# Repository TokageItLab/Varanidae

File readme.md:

# Varanidae

## Consepts / Ideology

This keyboard layout may look pretty Mad and Hacky at some parts, but there are proper reasons for each of them.

<details>
<summary>Simple implementation</summary>

We are not electronics professionals and do not like to implement complex PCBs. SMT may be efficient in using reflow, but it is hard for beginners, so we only use Through-hole components.

And to make implementation easier, we need to adopt Elite-C. However, Elite-C requires more space, so we solved this problem by overlapping it with other switches using a tall pin header.

In addition, to simplify the CNC manufacturing process, we had to design a case that could be machined with a 3-axis CNC. This makes it possible to output cases with some CNC services without complex communication with the manufacturers.

</details>

<details>
<summary>Compact layout for international</summary>

When we work, we place the pen tablet in front of the keyboard, thus making the desk smaller. So we needed to make the keyboard as compact as possible.

So we omitted some **outdated** keys (PauseBreak/ScrollLock/Insert/CapsLock) and adopted a 6U space bar. This allows us to provide almost a full keyboard (or more) functionality and place keys for language switching.

</details>

<details>
<summary>Left-side pad</summary>

We work with Blender and a pen tablet. Then, we hold the pen in our right hand, so we prefer to place the numpad (which has a lot of camera shortcuts assigned) in the left-side of the keyboard.

</details>

<details>
<summary>F13-F24 keys</summary>

We favor the F13-F24 keys for shortcuts. They avoid conflicts with the default shortcuts of any software and they are useful for resident application shortcuts.

I recommend to all keyboard manufacturers worldwide to implement F13-24 keys instead of having macro keys, or to allow F13-F24 keys to be assigned to the macro keys.

</details>

<details>
<summary>Backspace and Enter are the end of the right</summary>

We do not want to make more distance between the mouse, trackball, or trackpad and the keyboard. Also, since we use the Backspace and Enter keys so often, having them to the right of those keys can cause us to press other keys by accident.

Moreover, as an overlooked point, if the right-side of the Backspace and Enter keys are free, we can put our hand there to rest.

</details>

<details>
<summary>Lined up arrow keys</summary>

On common keyboard layout them in an inverted T-shape, but on some keyboards they are frequently in a single row to omit spaces.

However, in that case, the order is generally: "Left", "Down", "Up", "Right".

Perhaps this is because that, when you play games that use the arrow keys with the index finger in the Left and ring finger in the Right home position, the middle finger muscle tendon is pulled toward the ring finger.

But out of the game, this is unnatural considering the affordances. In the script editor, Up means "back a line", so we think it would be more natural to have it next to Left which means "back a character".

So this keyboard adopts the order: "Left", "Up", "Down", "Right" as default.

</details>

<details>
<summary>Compressed numpad</summary>

We should not need uselessly large + and Enter keys on numpad. More to the point, NumLock is not needed either. In that case, four basic math symbols can be placed vertically in one column.

Also, in fact, it is possible to place the Home/End/PgUp/PgDn keys symmetrically with those four keys, so we integrated them into one island.

This makes it possible to place keys for line transitions or Blender shortcuts without placing them to the right of Backspace and Enter.

</details>

<details>
<summary>R4 Tilda</summary>

The last mad point is that placing the Tilda at the end of R4. Because it is not used that often or the cases where it is used are quite special.

I believe that it is most reasonable to put Tilda at the end of R4. You may see a layout similar to this on some keyboards, such as Toshiba - Dynabook, but I don't understand why R4 Tilda is not more common.

I am saddened that there is no R4 Tilde in any GMK sets (and the same applies to the keys in the columns at both ends of compressed numpad).

</details>

Now, we finally got a keyboard that is very reasonable for us.

We hope that this layout will become more common and that the R4 Tilde will be included in some GMK set, so we are releasing it as an open source keyboard.

The license is all that is written in this repository, so this is no needed thing, but if you have any information about a derivative product of Varanidae or the R4 Tilde, we would be glad to hear about that.

Of course, simple feedbacks are also welcome.

## Supported layout

The rotary encoder is assigned to the middle click and vertical scrolling by default.

Varanidae supports [VIA](https://usevia.app/), so the key/encoder assignments can be changed.

---

**Note:** This keyboard is mainly designed for Japanese users, but uses the US layout. If you are using a JIS keyboard on the system, you will need to select the US keyboard layout (101/102 keys keyboard) in the "Language Settings".

**For example in Windows 10:**

「設定」→「時刻と言語」→「言語」→「優先する言語」→「日本語: オプション」→「ハードウェア キーボード レイアウト」→「レイアウトを変更する」→「英語キーボード (101/102 キー)」

---

## Description

This repository contains:

- case
  - ai
    - Vector file of the plates
    - **The plates are assumed to be 2mm thick, please note when ordering plates using this file**
  - f3d
    - Fusion 360 project file of the case
  - step
    - STEP files for CNC, output from Fusion 360 project
    - It may be necessary to refer to the Fusion 360 project to determine the exact hole type
    - **If you make the order with these files, pay attention to the type of threaded holes[^1]**
- img
  - Images for the readme
- pcb
  - kicad
    - KiCad project files of the PCB (include exported Gerber files)

Is ordering CNC expensive and complicated? [Varanidae Soul](https://github.com/TokageItLab/Varanidae_Soul) the simplified version of Varanidae only requires acrylic plates and screws. It is reasonable choice to try the Varanidae layout.

## Other required components

### For the PCB
- MX Keycap set x1 (**6u centerd space is required**)
- MX stabilizer set x1 (**6u wire is required, PCB mounted is required if you use hybrid layout**)
- MX stem switches x110
- Diodes 1N4148 x110
- Rotary encoder EC11 x1 (EC11N1525404 or EC11N1525402 is recommended)
- Knob x1 (**14mm diameter or less are strongly recommended since the case hole diameter is 15mm for the knob**)
- Elite-C x1
- Pin headers 5mm height x29 (For Elite-C, so **x11 + x11 + x7** or **x12 + x12 + x5** is reccomended)

---

**Note:** If you don't use the "spring" pin headers and need to solder the pin headers to the PCB, be careful about the working sequence. You must solder only the pin headers before mounting the switch, and the Elite-C must be soldered after the switch is mounted.

---

### For the case

#### To screw the case and the main plate
- M3 screws 15mm x20

#### To screw the bottom plate
- M3 screws 8mm x4
- M3 pipe spacers 4mm x4

#### To assemble the case legs with screws
- M5 full thread screws 34mm x2
- M5 pipe spacers 20mm x2
- M5 cap nuts 4mm depth x2

---

**Note:** The length of the case leg screw should be calculated based on the length of the leg and the depth of the cap nut you wish to use. For example, the screw and nut length are calculated as follows:

```
screw length (34mm) = spacer length (20mm) + cap nut depth (4mm) + depth of the case threaded hole which will be inserted the screw (10mm)
```

---

## Using libraries

- [kbd](https://github.com/foostan/kbd) - foostan (MIT license)
- [keebio-components](https://github.com/keebio/keebio-components) - Keebio (MIT license)
- [Keebio-Parts.pretty](https://github.com/keebio/Keebio-Parts.pretty) - Keebio (MIT license)
- [KiCad Footprint Libraries](https://gitlab.com/kicad/libraries/kicad-footprints/-/tree/master?ref_type=heads) - KiCad ([KiCad Libraries License](https://gitlab.com/kicad/libraries/kicad-footprints/-/blob/master/LICENSE.md))
- [MX_Alps_Hybrid](https://github.com/ai03-2725/MX_Alps_Hybrid/tree/master/Alps_Only.pretty) ([my fork](https://github.com/TokageItLab/MX_Alps_Hybrid/tree/Varanidae)) - ai03 (MIT license)

## Special thanks (Artisan keycaps for the thumbnail)

- Birb - [KEYMAKER](https://www.keymakerartisankeycaps.com/)
- Space 無 - [GEEKKEEY](https://www.instagram.com/geekkeey/)
- The 925 - [THOK](https://thok.design/)
- THINK - [BOXXX KEYCAP](https://boxxx.booth.pm/)

## License

MIT license except that the Tokage IT Lab.'s logo is CC BY-NC-ND 4.0. This means that if you want to manufacture and sell the derived PCBs, you can do so by removing the Tokage IT Lab.'s logo from them[^2].

Also, if you redistribute the libraries used in the KiCad projects, you must respect their libraries' license.

[^1]: One actual case that has happened is that when using [meviy](https://meviy.misumi-ec.com), the M5 screw holes for screwing the feet to the bottom case are detected as not being drilled all the way through (they look through, but are not drilled all the way through). In this case, you need to specify to drill the M5 hole all the way through on the meviy web app.

[^2]: However, credit must be placed somewhere for derivatives to follow the MIT license. This doesn't mean printing the credit on the PCB, but only having it somewhere, such as on a github repository, promotional page, paper manual or etc.

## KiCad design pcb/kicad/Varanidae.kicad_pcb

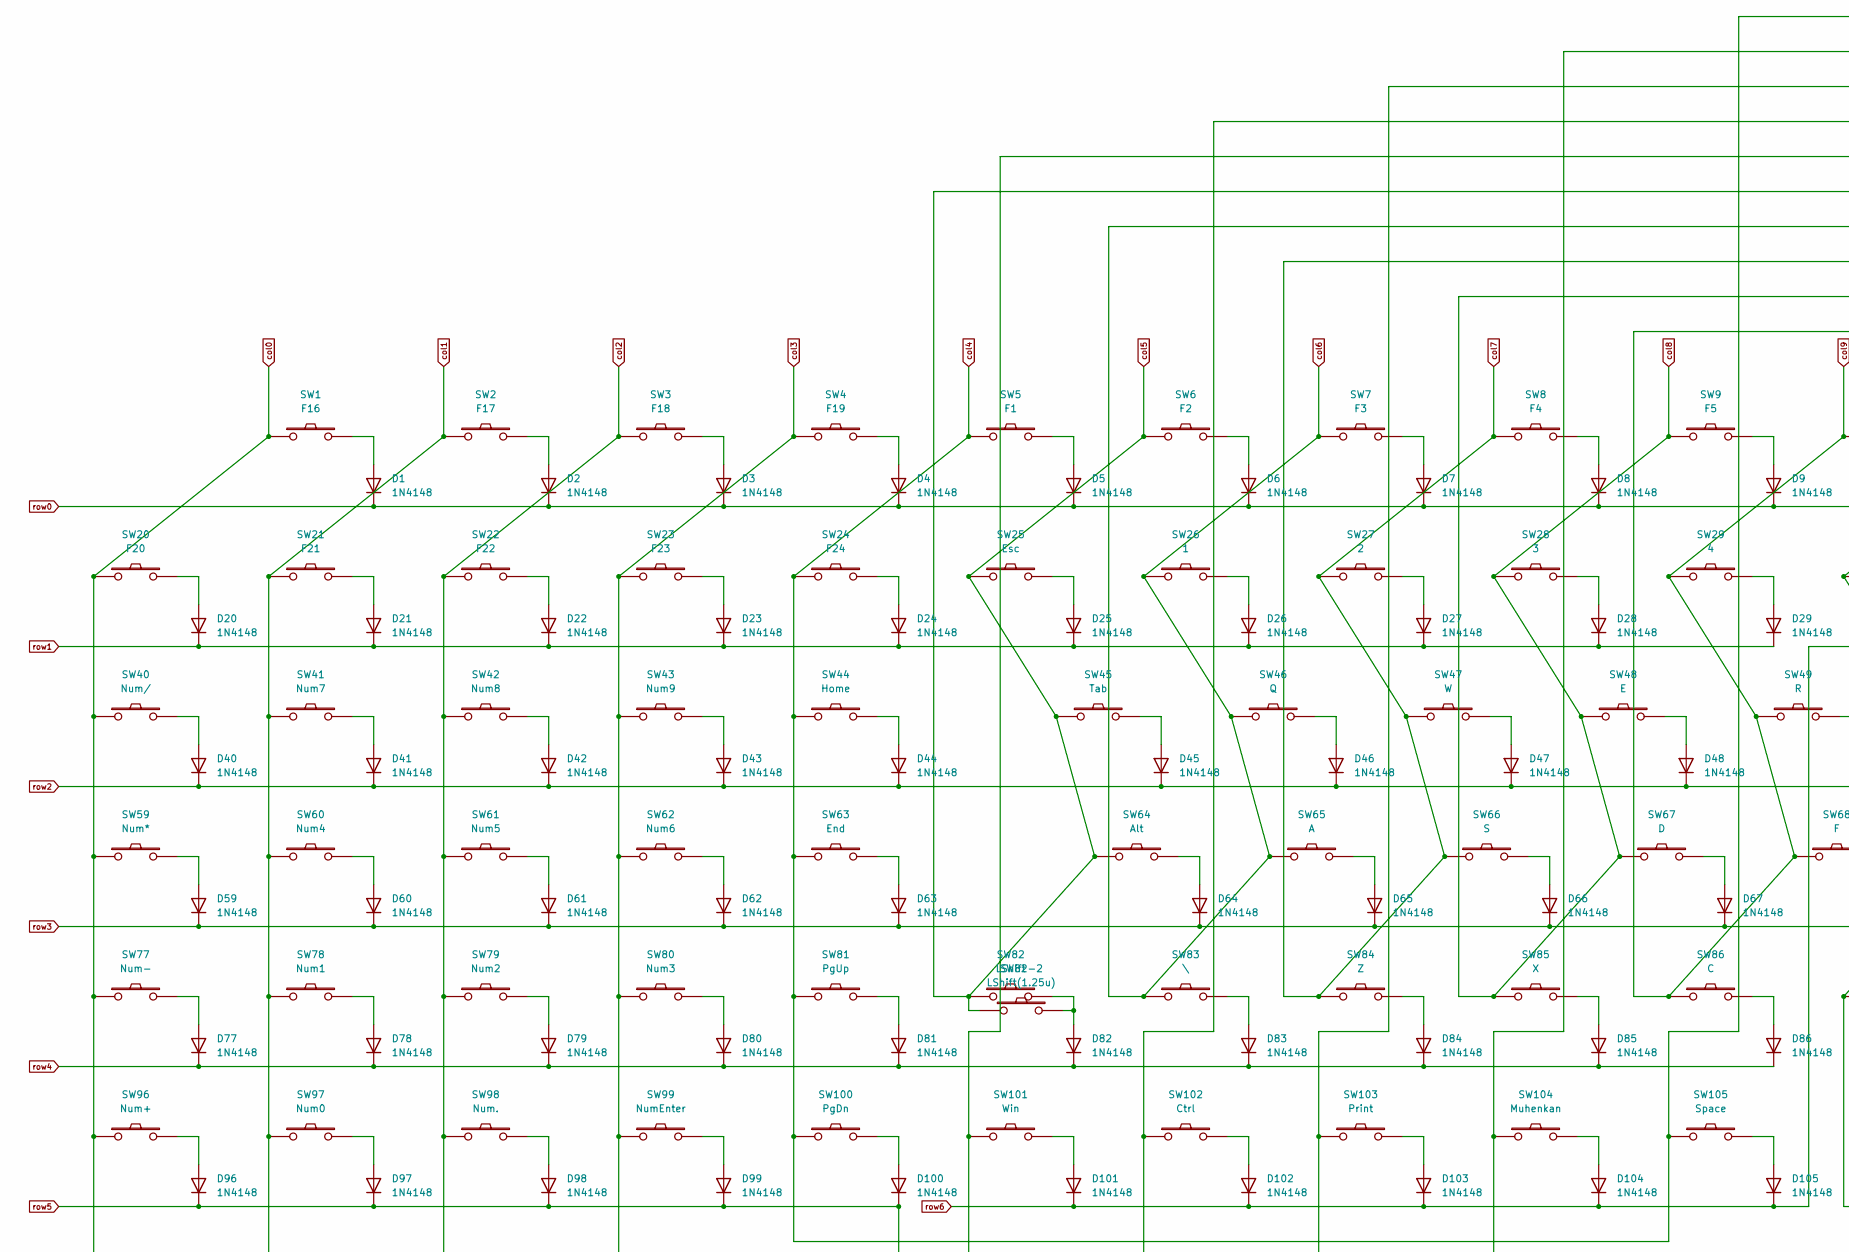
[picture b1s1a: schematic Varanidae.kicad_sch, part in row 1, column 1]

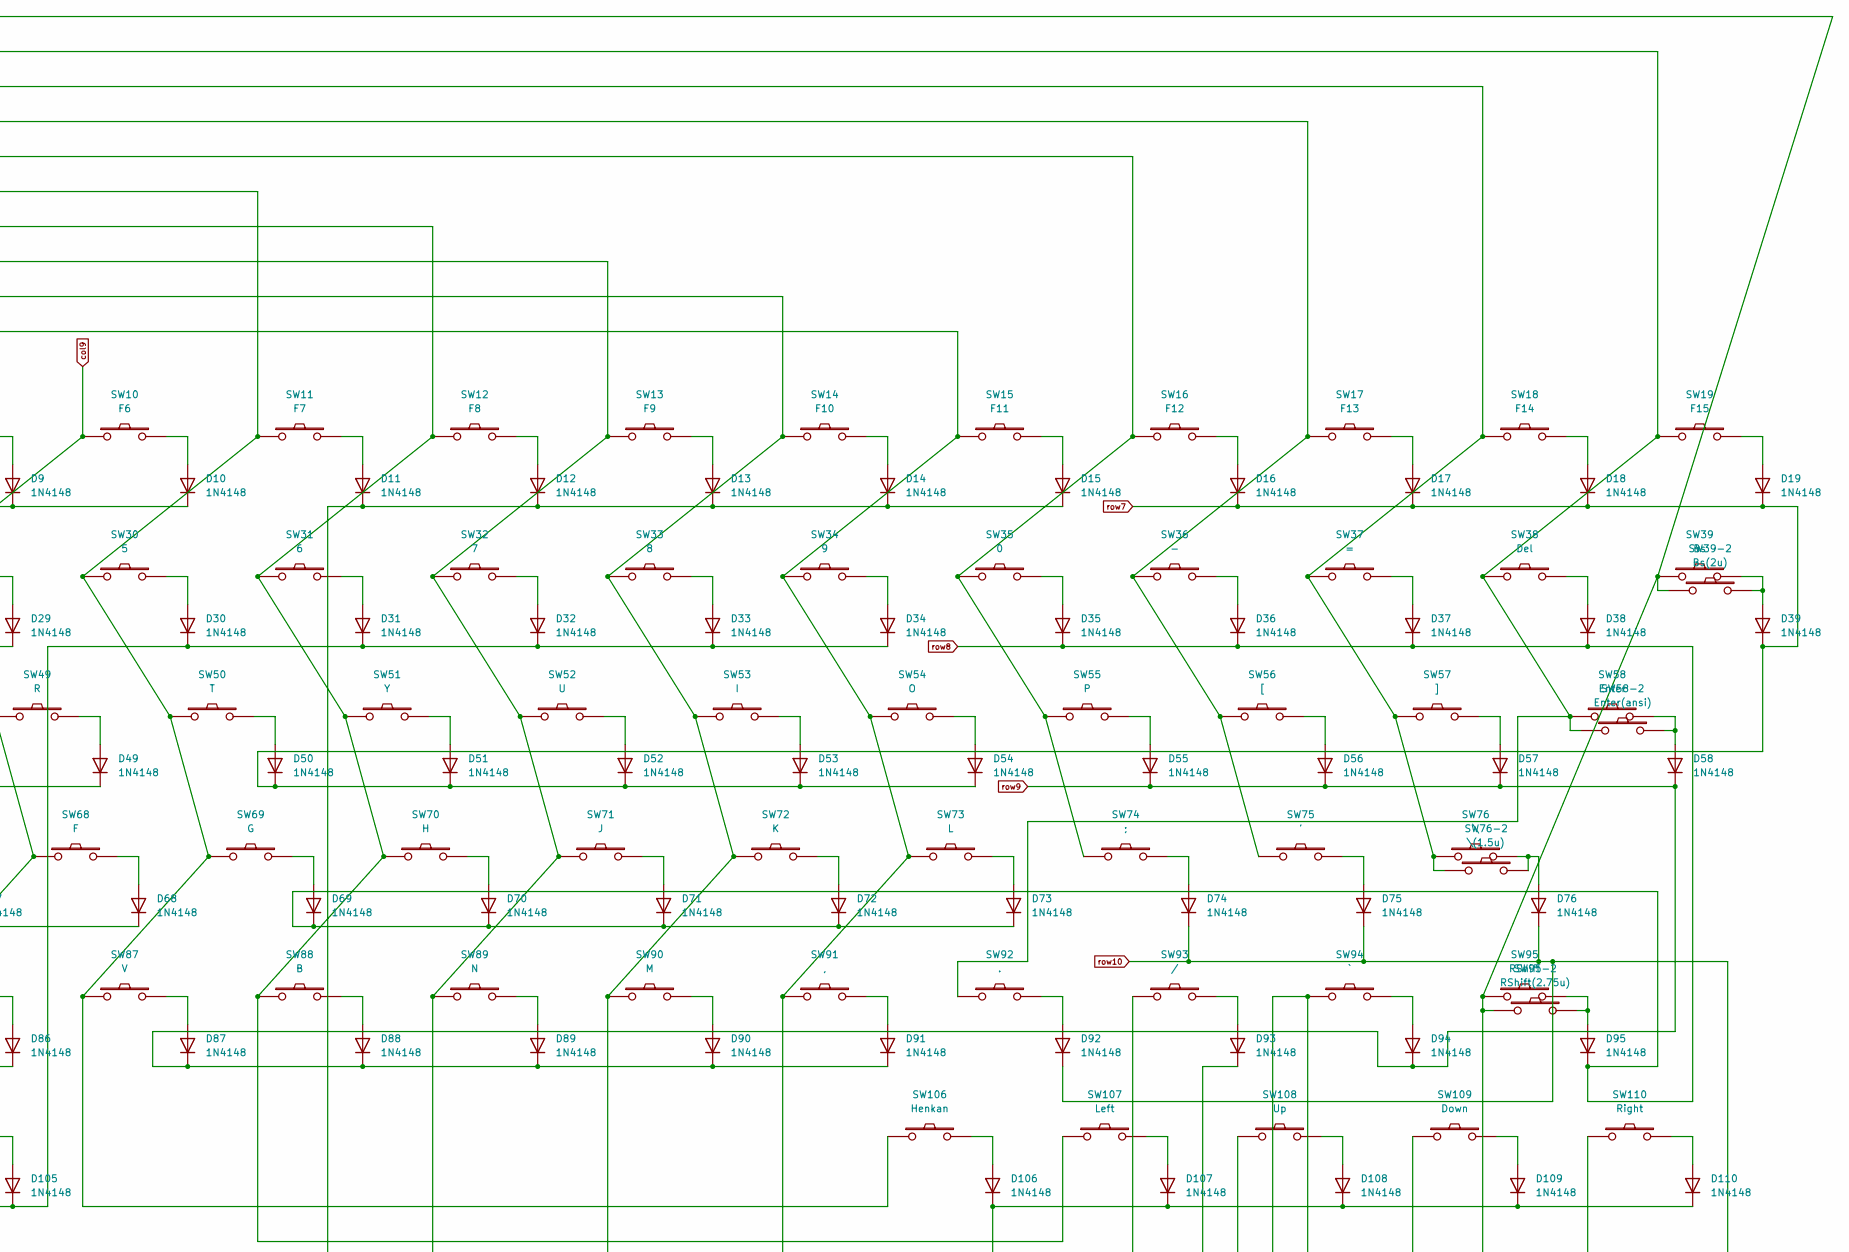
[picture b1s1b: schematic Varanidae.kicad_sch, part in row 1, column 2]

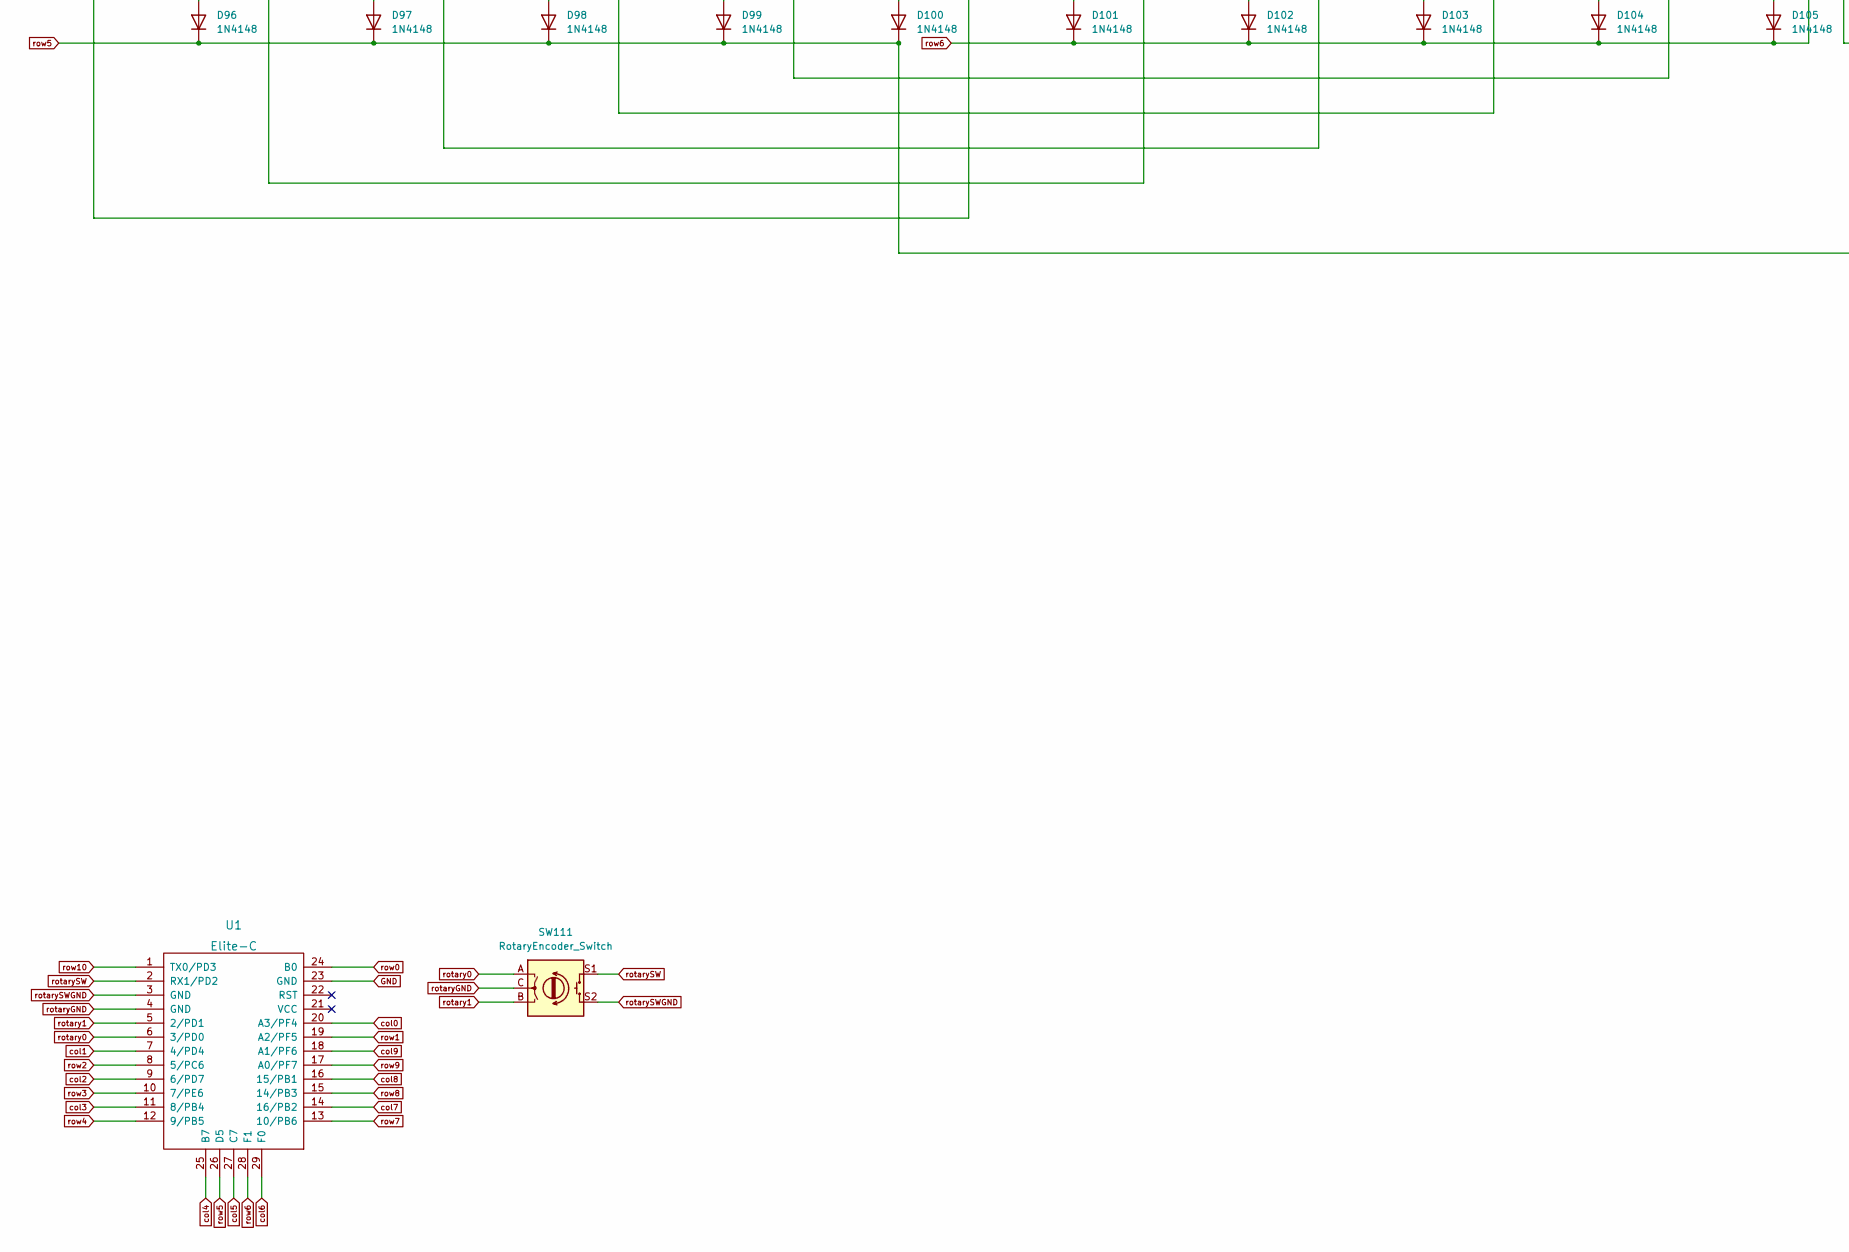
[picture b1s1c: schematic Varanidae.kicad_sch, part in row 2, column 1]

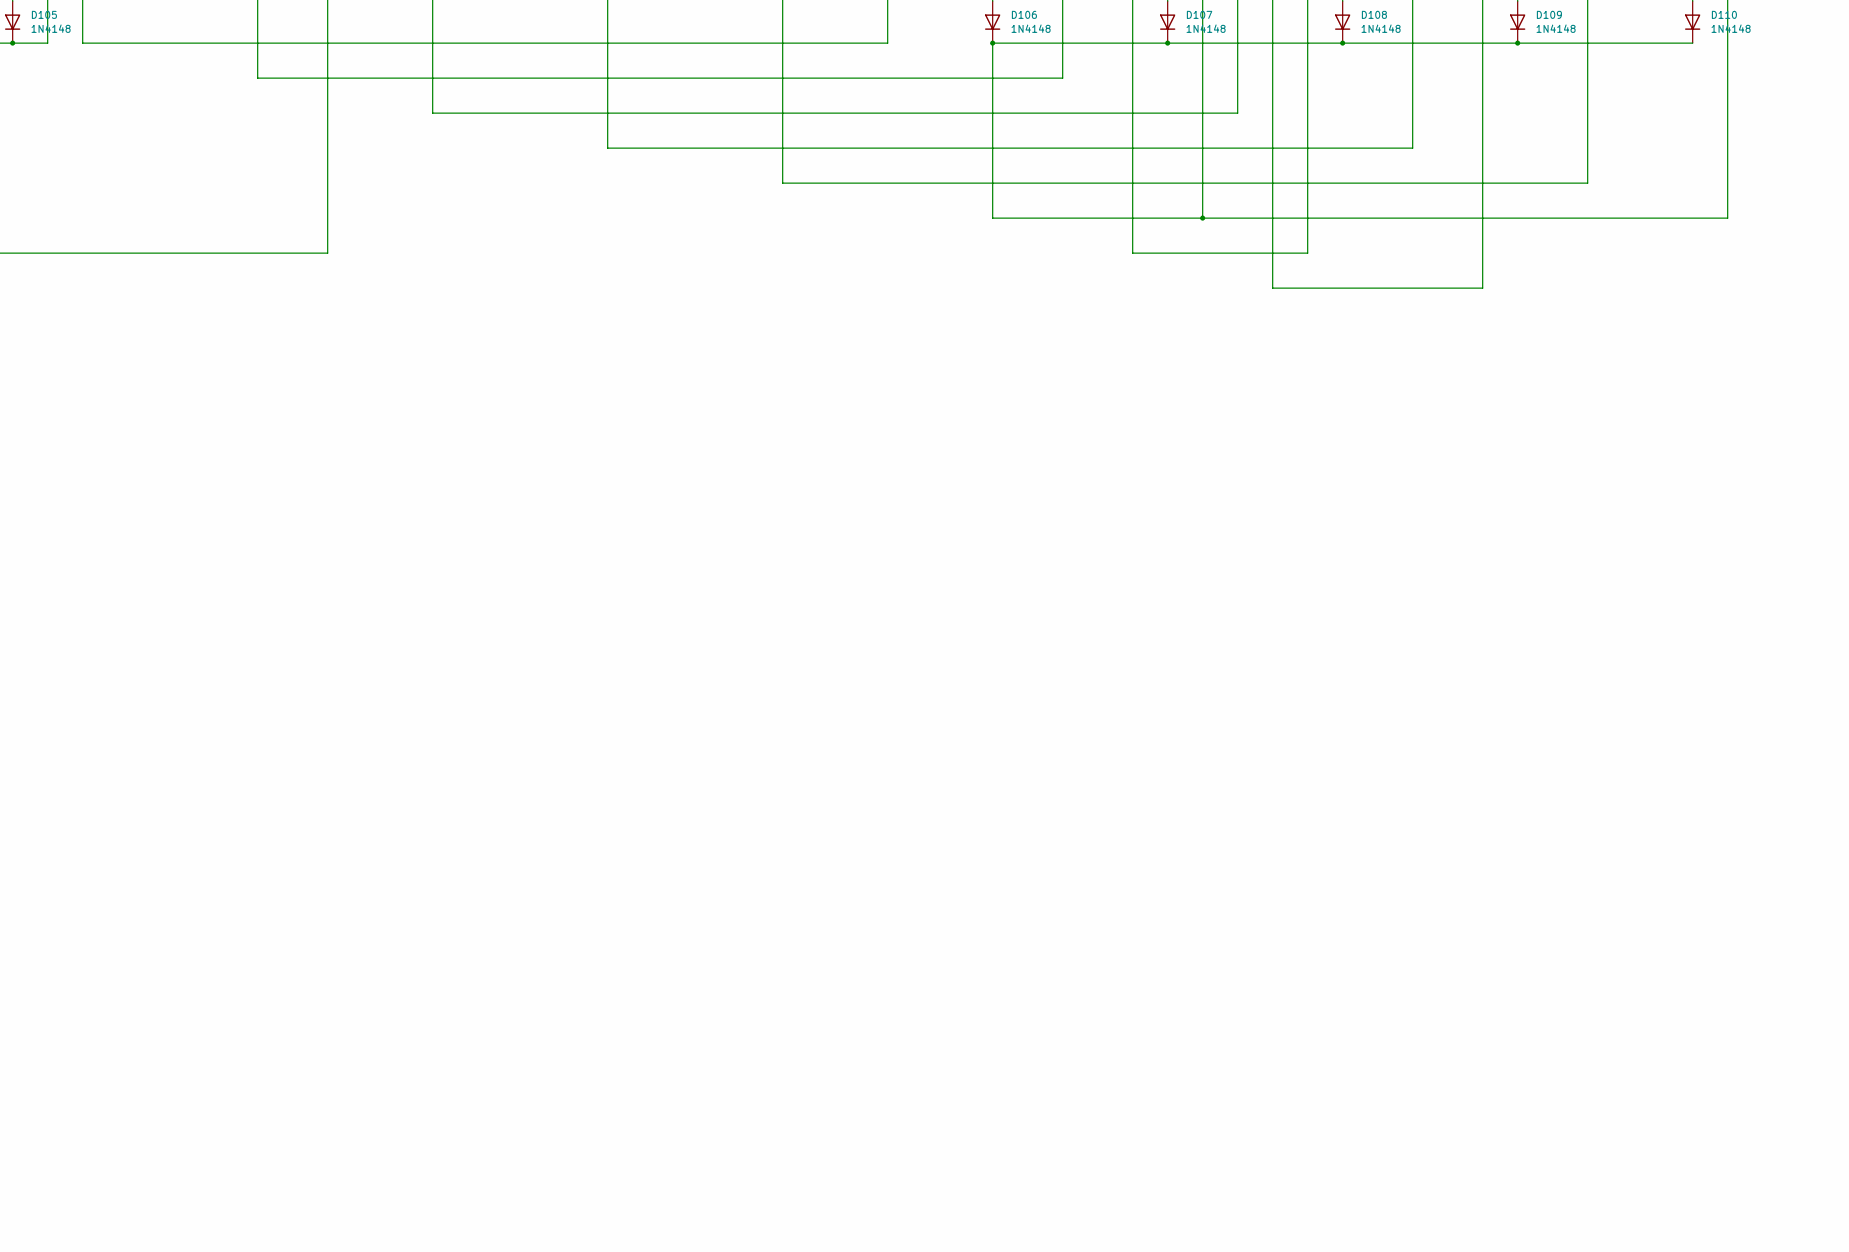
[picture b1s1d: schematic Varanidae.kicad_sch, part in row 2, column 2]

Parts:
D1, D2, D3, D4, D5, D6, D7, D8, D9, D10, D11, D12, D13, D14, D15, D16, D17, D18, D19, D20, D21, D22, D23, D24, D25, D26, D27, D28, D29, D30, D31, D32, D33, D34, D35, D36, D37, D38, D39, D40, D41, D42, D43, D44, D45, D46, D47, D48, D49, D50, D51, D52, D53, D54, D55, D56, D57, D58, D59, D60, D61, D62, D63, D64, D65, D66, D67, D68, D69, D70, D71, D72, D73, D74, D75, D76, D77, D78, D79, D80, D81, D82, D83, D84, D85, D86, D87, D88, D89, D90, D91, D92, D93, D94, D95, D96, D97, D98, D99, D100, D101, D102, D103, D104, D105, D106, D107, D108, D109, D110: 1N4148; D_DO-35_SOD27_P7.62mm_Horizontal
SW1: F16; MXOnly-1U-NoLED
SW2: F17; MXOnly-1U-NoLED
SW3: F18; MXOnly-1U-NoLED
SW4: F19; MXOnly-1U-NoLED
SW5: F1; MXOnly-1U-NoLED
SW6: F2; MXOnly-1U-NoLED
SW7: F3; MXOnly-1U-NoLED
SW8: F4; MXOnly-1U-NoLED
SW9: F5; MXOnly-1U-NoLED
SW10: F6; MXOnly-1U-NoLED
SW11: F7; MXOnly-1U-NoLED
SW12: F8; MXOnly-1U-NoLED
SW13: F9; MXOnly-1U-NoLED
SW14: F10; MXOnly-1U-NoLED
SW15: F11; MXOnly-1U-NoLED
SW16: F12; MXOnly-1U-NoLED
SW17: F13; MXOnly-1U-NoLED
SW18: F14; MXOnly-1U-NoLED
SW19: F15; MXOnly-1U-NoLED
SW20: F20; MXOnly-1U-NoLED
SW21: F21; MXOnly-1U-NoLED
SW22: F22; MXOnly-1U-NoLED
SW23: F23; MXOnly-1U-NoLED
SW24: F24; MXOnly-1U-NoLED
SW25: Esc; MXOnly-1U-NoLED
SW26: 1; MXOnly-1U-NoLED
SW27: 2; MXOnly-1U-NoLED
SW28: 3; MXOnly-1U-NoLED
SW29: 4; MXOnly-1U-NoLED
SW30: 5; MXOnly-1U-NoLED
SW31: 6; MXOnly-1U-NoLED
SW32: 7; MXOnly-1U-NoLED
SW33: 8; MXOnly-1U-NoLED
SW34: 9; MXOnly-1U-NoLED
SW35: 0; MXOnly-1U-NoLED
SW36: -; MXOnly-1U-NoLED
SW37: =; MXOnly-1U-NoLED
SW38: Del; MXOnly-1U-NoLED
SW39: Bs; MXOnly-1U-ROTATED-NoLED
SW39-2: Bs(2u); MXOnly-2U-NoLED
SW40: Num/; MXOnly-1U-NoLED
SW41: Num7; MXOnly-1U-NoLED
SW42: Num8; MXOnly-1U-NoLED
SW43: Num9; MXOnly-1U-NoLED
SW44: Home; MXOnly-1U-NoLED
SW45: Tab; MXOnly-1U-NoLED
SW46: Q; MXOnly-1U-NoLED
SW47: W; MXOnly-1U-NoLED
SW48: E; MXOnly-1U-NoLED
SW49: R; MXOnly-1U-NoLED
SW50: T; MXOnly-1U-NoLED
SW51: Y; MXOnly-1U-NoLED
SW52: U; MXOnly-1U-NoLED
SW53: I; MXOnly-1U-NoLED
SW54: O; MXOnly-1U-NoLED
SW55: P; MXOnly-1U-NoLED
SW56: [; MXOnly-1U-NoLED
SW57: ]; MXOnly-1U-NoLED
SW58: Enter; MXOnly-ISO-ROTATED-ReversedStabilizers-NoLED
SW58-2: Enter(ansi); MXOnly-2.25U-ReversedStabilizers-NoLED
SW59: Num*; MXOnly-1U-NoLED
SW60: Num4; MXOnly-1U-NoLED
SW61: Num5; MXOnly-1U-NoLED
SW62: Num6; MXOnly-1U-NoLED
SW63: End; MXOnly-1U-NoLED
SW64: Alt; MXOnly-1.75U-NoLED
SW65: A; MXOnly-1U-NoLED
SW66: S; MXOnly-1U-NoLED
SW67: D; MXOnly-1U-NoLED
SW68: F; MXOnly-1U-NoLED
SW69: G; MXOnly-1U-NoLED
SW70: H; MXOnly-1U-NoLED
SW71: J; MXOnly-1U-NoLED
SW72: K; MXOnly-1U-NoLED
SW73: L; MXOnly-1U-NoLED
SW74: ;; MXOnly-1U-NoLED
SW75: '; MXOnly-1U-NoLED
SW76, SW83: \; MXOnly-1U-NoLED
SW76-2: \(1.5u); MXOnly-1.5U-ROTATED-NoLED
SW77: Num-; MXOnly-1U-NoLED
SW78: Num1; MXOnly-1U-NoLED
SW79: Num2; MXOnly-1U-NoLED
SW80: Num3; MXOnly-1U-NoLED
SW81: PgUp; MXOnly-1U-NoLED
SW82: LShift; MXOnly-2.25U-NoLED
SW82-2: LShift(1.25u); MXOnly-1.25U-NoLED
SW84: Z; MXOnly-1U-NoLED
SW85: X; MXOnly-1U-NoLED
SW86: C; MXOnly-1U-NoLED
SW87: V; MXOnly-1U-NoLED
SW88: B; MXOnly-1U-NoLED
SW89: N; MXOnly-1U-NoLED
SW90: M; MXOnly-1U-NoLED
SW91: ,; MXOnly-1U-NoLED
SW92: .; MXOnly-1U-NoLED
SW93: /; MXOnly-1U-NoLED
SW94: `; MXOnly-1U-NoLED
SW95: RShift; MXOnly-1.75U-ROTATED-NoLED
SW95-2: RShift(2.75u); MXOnly-2.75U-NoLED
SW96: Num+; MXOnly-1U-NoLED
SW97: Num0; MXOnly-1U-NoLED
SW98: Num.; MXOnly-1U-NoLED
SW99: NumEnter; MXOnly-1U-NoLED
SW100: PgDn; MXOnly-1U-NoLED
SW101: Win; MXOnly-1U-NoLED
SW102: Ctrl; MXOnly-1U-NoLED
SW103: Print; MXOnly-1U-NoLED
SW104: Muhenkan; MXOnly-1U-NoLED
SW105: Space; MXOnly-6U-Centered-ReversedStabilizers-NoLED
SW106: Henkan; MXOnly-1U-NoLED
SW107: Left; MXOnly-1U-NoLED
SW108: Up; MXOnly-1U-NoLED
SW109: Down; MXOnly-1U-NoLED
SW110: Right; MXOnly-1U-NoLED
SW111: RotaryEncoder_Switch; RotaryEncoder_Alps_EC11E-Switch_Vertical_H20mm
U1: Elite-C; Elite-C-conthrough

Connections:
GND: U1.23 (GND)
unnamed: D1.2 (A), SW1.2
unnamed: D2.2 (A), SW2.2
unnamed: D3.2 (A), SW3.2
unnamed: D4.2 (A), SW4.2
unnamed: D5.2 (A), SW5.2
unnamed: D6.2 (A), SW6.2
unnamed: D7.2 (A), SW7.2
unnamed: D8.2 (A), SW8.2
unnamed: D9.2 (A), SW9.2
unnamed: D10.2 (A), SW10.2
unnamed: D11.2 (A), SW11.2
unnamed: D12.2 (A), SW12.2
unnamed: D13.2 (A), SW13.2
unnamed: D14.2 (A), SW14.2
unnamed: D15.2 (A), SW15.2
unnamed: D16.2 (A), SW16.2
unnamed: D17.2 (A), SW17.2
unnamed: D18.2 (A), SW18.2
unnamed: D19.2 (A), SW19.2
unnamed: D20.2 (A), SW20.2
unnamed: D21.2 (A), SW21.2
unnamed: D22.2 (A), SW22.2
unnamed: D23.2 (A), SW23.2
unnamed: D24.2 (A), SW24.2
unnamed: D25.2 (A), SW25.2
unnamed: D26.2 (A), SW26.2
unnamed: D27.2 (A), SW27.2
unnamed: D28.2 (A), SW28.2
unnamed: D29.2 (A), SW29.2
unnamed: D30.2 (A), SW30.2
unnamed: D31.2 (A), SW31.2
unnamed: D32.2 (A), SW32.2
unnamed: D33.2 (A), SW33.2
unnamed: D34.2 (A), SW34.2
unnamed: D35.2 (A), SW35.2
unnamed: D36.2 (A), SW36.2
unnamed: D37.2 (A), SW37.2
unnamed: D38.2 (A), SW38.2
unnamed: D39.2 (A), SW39.2, SW39-2.2
unnamed: D40.2 (A), SW40.2
unnamed: D41.2 (A), SW41.2
unnamed: D42.2 (A), SW42.2
unnamed: D43.2 (A), SW43.2
unnamed: D44.2 (A), SW44.2
unnamed: D45.2 (A), SW45.2
unnamed: D46.2 (A), SW46.2
unnamed: D47.2 (A), SW47.2
unnamed: D48.2 (A), SW48.2
unnamed: D49.2 (A), SW49.2
unnamed: D50.2 (A), SW50.2
unnamed: D51.2 (A), SW51.2
unnamed: D52.2 (A), SW52.2
unnamed: D53.2 (A), SW53.2
unnamed: D54.2 (A), SW54.2
unnamed: D55.2 (A), SW55.2
unnamed: D56.2 (A), SW56.2
unnamed: D57.2 (A), SW57.2
unnamed: D58.2 (A), SW58.2, SW58-2.2
unnamed: D59.2 (A), SW59.2
unnamed: D60.2 (A), SW60.2
unnamed: D61.2 (A), SW61.2
unnamed: D62.2 (A), SW62.2
unnamed: D63.2 (A), SW63.2
unnamed: D64.2 (A), SW64.2
unnamed: D65.2 (A), SW65.2
unnamed: D66.2 (A), SW66.2
unnamed: D67.2 (A), SW67.2
unnamed: D68.2 (A), SW68.2
unnamed: D69.2 (A), SW69.2
unnamed: D70.2 (A), SW70.2
unnamed: D71.2 (A), SW71.2
unnamed: D72.2 (A), SW72.2
unnamed: D73.2 (A), SW73.2
unnamed: D74.2 (A), SW74.2
unnamed: D75.2 (A), SW75.2
unnamed: D76.2 (A), SW76.2, SW76-2.2
unnamed: D77.2 (A), SW77.2
unnamed: D78.2 (A), SW78.2
unnamed: D79.2 (A), SW79.2
unnamed: D80.2 (A), SW80.2
unnamed: D81.2 (A), SW81.2
unnamed: D82.2 (A), SW82.2, SW82-2.2
unnamed: D83.2 (A), SW83.2
unnamed: D84.2 (A), SW84.2
unnamed: D85.2 (A), SW85.2
unnamed: D86.2 (A), SW86.2
unnamed: D87.2 (A), SW87.2
unnamed: D88.2 (A), SW88.2
unnamed: D89.2 (A), SW89.2
unnamed: D90.2 (A), SW90.2
unnamed: D91.2 (A), SW91.2
unnamed: D92.2 (A), SW92.2
unnamed: D93.2 (A), SW93.2
unnamed: D94.2 (A), SW94.2
unnamed: D95.2 (A), SW95.2, SW95-2.2
unnamed: D96.2 (A), SW96.2
unnamed: D97.2 (A), SW97.2
unnamed: D98.2 (A), SW98.2
unnamed: D99.2 (A), SW99.2
unnamed: D100.2 (A), SW100.2
unnamed: D101.2 (A), SW101.2
unnamed: D102.2 (A), SW102.2
unnamed: D103.2 (A), SW103.2
unnamed: D104.2 (A), SW104.2
unnamed: D105.2 (A), SW105.2
unnamed: D106.2 (A), SW106.2
unnamed: D107.2 (A), SW107.2
unnamed: D108.2 (A), SW108.2
unnamed: D109.2 (A), SW109.2
unnamed: D110.2 (A), SW110.2
col0: SW1.1, SW16.1, SW20.1, SW35.1, SW40.1, SW55.1, SW59.1, SW74.1, SW77.1, SW96.1, SW101.1, U1.20 (A3/PF4)
col1: SW2.1, SW17.1, SW21.1, SW36.1, SW41.1, SW56.1, SW60.1, SW75.1, SW78.1, SW97.1, SW102.1, U1.7 (4/PD4)
col2: SW3.1, SW18.1, SW22.1, SW37.1, SW42.1, SW57.1, SW61.1, SW76.1, SW76-2.1, SW79.1, SW98.1, SW103.1, U1.9 (6/PD7)
col3: SW4.1, SW19.1, SW23.1, SW38.1, SW43.1, SW58.1, SW58-2.1, SW62.1, SW80.1, SW92.1, SW99.1, SW104.1, U1.11 (8/PB4)
col4: SW5.1, SW24.1, SW39.1, SW39-2.1, SW44.1, SW63.1, SW81.1, SW93.1, SW94.1, SW95.1, SW95-2.1, SW100.1, SW105.1, U1.25 (B7)
col5: SW6.1, SW11.1, SW25.1, SW30.1, SW45.1, SW50.1, SW64.1, SW69.1, SW82.1, SW82-2.1, SW87.1, SW106.1, U1.27 (C7)
col6: SW7.1, SW12.1, SW26.1, SW31.1, SW46.1, SW51.1, SW65.1, SW70.1, SW83.1, SW88.1, SW107.1, U1.29 (F0)
col7: SW8.1, SW13.1, SW27.1, SW32.1, SW47.1, SW52.1, SW66.1, SW71.1, SW84.1, SW89.1, SW108.1, U1.14 (16/PB2)
col8: SW9.1, SW14.1, SW28.1, SW33.1, SW48.1, SW53.1, SW67.1, SW72.1, SW85.1, SW90.1, SW109.1, U1.16 (15/PB1)
col9: SW10.1, SW15.1, SW29.1, SW34.1, SW49.1, SW54.1, SW68.1, SW73.1, SW86.1, SW91.1, SW110.1, U1.18 (A1/PF6)
rotary0: SW111.A, U1.6 (3/PD0)
rotary1: SW111.B, U1.5 (2/PD1)
rotaryGND: SW111.C, U1.4 (GND)
rotarySW: SW111.S1, U1.2 (RX1/PD2)
rotarySWGND: SW111.S2, U1.3 (GND)
row0: D1.1 (K), D2.1 (K), D3.1 (K), D4.1 (K), D5.1 (K), D6.1 (K), D7.1 (K), D8.1 (K), D9.1 (K), D10.1 (K), U1.24 (B0)
row1: D20.1 (K), D21.1 (K), D22.1 (K), D23.1 (K), D24.1 (K), D25.1 (K), D26.1 (K), D27.1 (K), D28.1 (K), D29.1 (K), U1.19 (A2/PF5)
row2: D40.1 (K), D41.1 (K), D42.1 (K), D43.1 (K), D44.1 (K), D45.1 (K), D46.1 (K), D47.1 (K), D48.1 (K), D49.1 (K), U1.8 (5/PC6)
row3: D59.1 (K), D60.1 (K), D61.1 (K), D62.1 (K), D63.1 (K), D64.1 (K), D65.1 (K), D66.1 (K), D67.1 (K), D68.1 (K), U1.10 (7/PE6)
row4: D77.1 (K), D78.1 (K), D79.1 (K), D80.1 (K), D81.1 (K), D82.1 (K), D83.1 (K), D84.1 (K), D85.1 (K), D86.1 (K), U1.12 (9/PB5)
row5: D11.1 (K), D12.1 (K), D13.1 (K), D14.1 (K), D15.1 (K), D96.1 (K), D97.1 (K), D98.1 (K), D99.1 (K), D100.1 (K), U1.26 (D5)
row6: D30.1 (K), D31.1 (K), D32.1 (K), D33.1 (K), D34.1 (K), D101.1 (K), D102.1 (K), D103.1 (K), D104.1 (K), D105.1 (K), U1.28 (F1)
row7: D16.1 (K), D17.1 (K), D18.1 (K), D19.1 (K), D39.1 (K), D50.1 (K), D51.1 (K), D52.1 (K), D53.1 (K), D54.1 (K), U1.13 (10/PB6)
row8: D35.1 (K), D36.1 (K), D37.1 (K), D38.1 (K), D69.1 (K), D70.1 (K), D71.1 (K), D72.1 (K), D73.1 (K), D95.1 (K), U1.15 (14/PB3)
row9: D55.1 (K), D56.1 (K), D57.1 (K), D58.1 (K), D87.1 (K), D88.1 (K), D89.1 (K), D90.1 (K), D91.1 (K), D94.1 (K), U1.17 (A0/PF7)
row10: D74.1 (K), D75.1 (K), D76.1 (K), D92.1 (K), D93.1 (K), D106.1 (K), D107.1 (K), D108.1 (K), D109.1 (K), D110.1 (K), U1.1 (TX0/PD3)

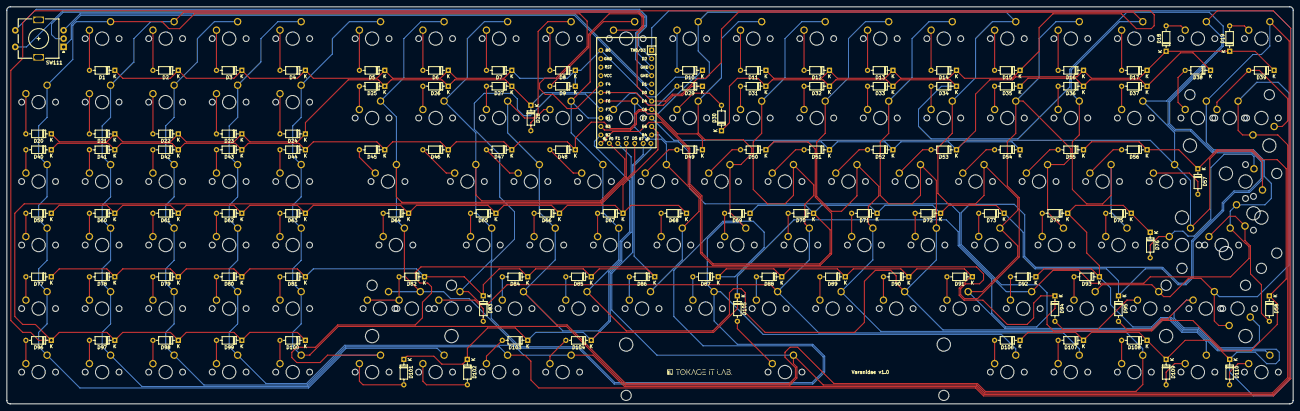
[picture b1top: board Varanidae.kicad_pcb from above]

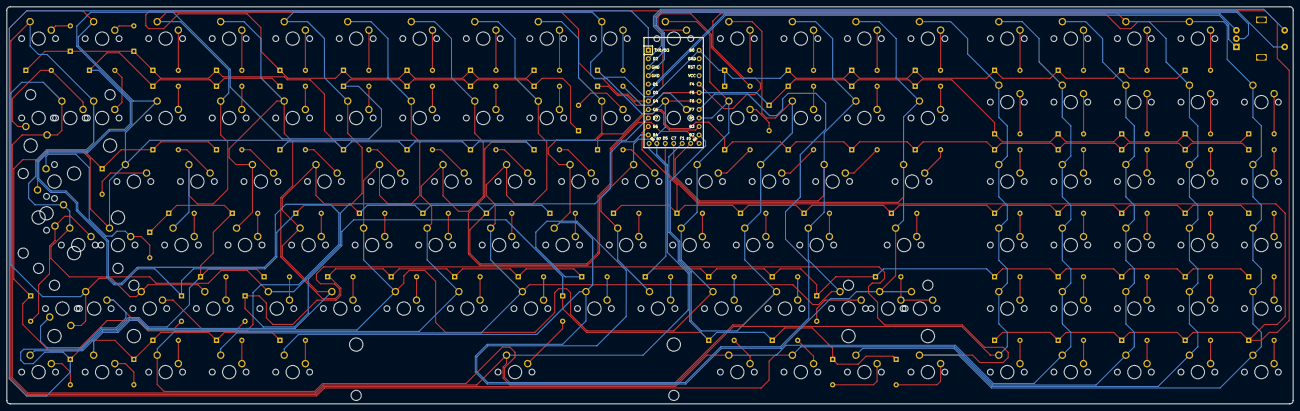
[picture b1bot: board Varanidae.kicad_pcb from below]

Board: 2 copper layers, 385.8 x 119.1 mm, 227 parts (116 on the bottom side), 136 nets.
